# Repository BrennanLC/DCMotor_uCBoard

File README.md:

DCMotor_uCBoard
===============

ATmega328P Microcontroller Board with 2-CH DC Motor Driver

Design has not yet been verified. Build at your own risk!

Files:

MDM00001.sch - Board schematic eagle file

MDM00001.pdf - Board schematic PDF file

MDM00001.brd - Board layout eagle file

MDM00001Board.pdf - Board layout PDF file

schematic and board layout built with Eagle 6.4.0 Standard. More info and 
download available here:

https://www.cadsoftusa.com/

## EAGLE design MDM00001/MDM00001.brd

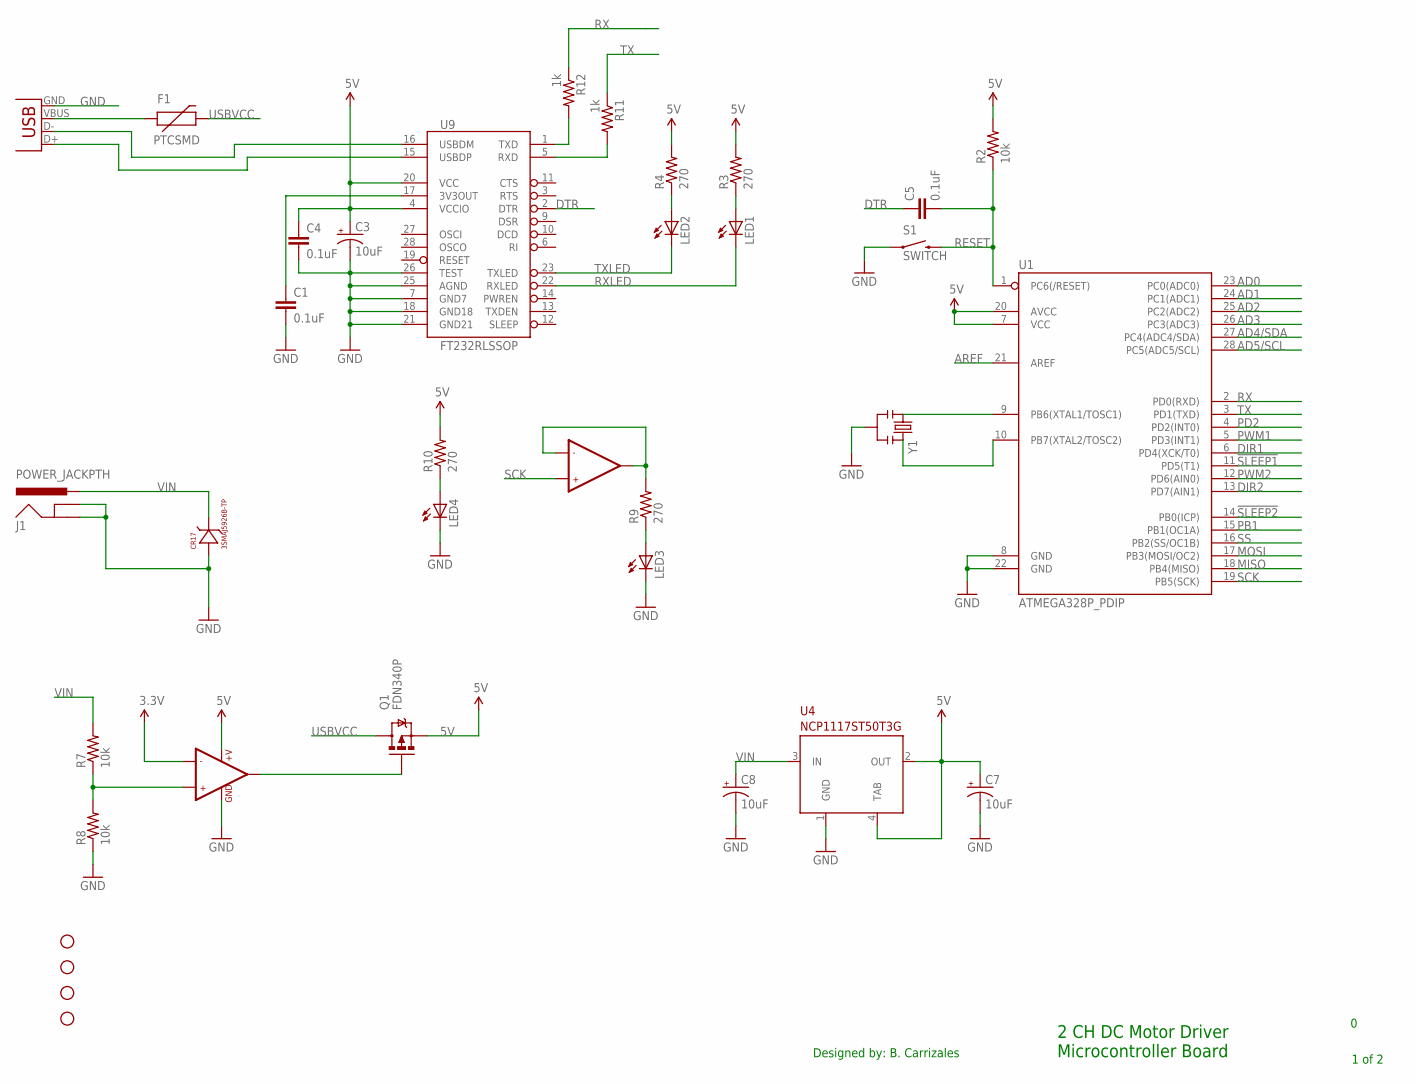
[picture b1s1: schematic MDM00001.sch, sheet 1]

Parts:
C1, C4, C5: 0.1uF; 0603-CAP
C3, C7, C8: 10uF; PANASONIC_BMIN
CR17: 3SMAJ5926B-TP; DO-214AC
F1: PTCSMD; PTC-1206
J1: POWER_JACKPTH; POWER_JACK_PTH
JP2: USBSMD; USB-MINIB
LED1, LED2, LED3, LED4: LED0603; LED-0603
Q1: FDN340P; SOT23-3
R2, R7, R8: 10k; 0603-RES
R3, R4, R9, R10: 270; 0603-RES
R11, R12: 1k; 0603-RES
S1: SWITCH; TACTILE-PTH
STANDOFF1, STANDOFF2, STANDOFF3, STANDOFF4: STAND-OFF
U1: ATMEGA328P_PDIP; DIL28-3
U4: NCP1117ST50T3G; SOT223
U9: FT232RLSSOP; SSOP28DB
U$3: LMV358; SO08
Y1: RESONATORPTH; RESONATOR-PTH

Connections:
3.3V: U$3.2 (-IN1)
5V: C3.+, C4.1, C7.+, Q1.2 (S), R2.2, R3.2, R4.2, R10.2, U1.7 (VCC), U1.20 (AVCC), U4.2 (OUT), U4.4 (TAB), U9.4 (VCCIO), U9.20 (VCC), U$3.8 (+V); also elsewhere on the board
!SLEEP1: U1.11 (PD5(T1)); also elsewhere on the board
!SLEEP2: U1.14 (PB0(ICP)); also elsewhere on the board
AD0: U1.23 (PC0(ADC0)); also elsewhere on the board
AD1: U1.24 (PC1(ADC1)); also elsewhere on the board
AD2: U1.25 (PC2(ADC2)); also elsewhere on the board
AD3: U1.26 (PC3(ADC3))
AD4/SDA: U1.27 (PC4(ADC4/SDA))
AD5/SCL: U1.28 (PC5(ADC5/SCL))
AREF: U1.21 (AREF)
DIR1: U1.6 (PD4(XCK/T0)); also elsewhere on the board
DIR2: U1.13 (PD7(AIN1)); also elsewhere on the board
DTR: C5.1, U9.2 (DTR)
GND: C1.2, C3.-, C4.2, C7.-, C8.-, CR17.AN, J1.GND, J1.GNDBREAK, JP2.GND, LED3.C, LED4.C, R8.1, S1.1, U1.8 (GND), U1.22 (GND), U4.1 (GND), U9.7 (GND7), U9.18 (GND18), U9.21 (GND21), U9.25 (AGND), U9.26 (TEST), U$3.4 (GND), Y1.2; also elsewhere on the board
MISO: U1.18 (PB4(MISO)); also elsewhere on the board
MOSI: U1.17 (PB3(MOSI/OC2)); also elsewhere on the board
unnamed: U1.9 (PB6(XTAL1/TOSC1)), Y1.1
unnamed: U1.10 (PB7(XTAL2/TOSC2)), Y1.3
unnamed: JP2.D-, U9.16 (USBDM)
unnamed: JP2.D+, U9.15 (USBDP)
unnamed: F1.1, JP2.VBUS
unnamed: LED2.A, R4.1
unnamed: LED1.A, R3.1
unnamed: R12.2, U9.1 (TXD)
unnamed: R11.2, U9.5 (RXD)
unnamed: R7.1, R8.2, U$3.3 (+IN1)
unnamed: LED3.A, R9.1
unnamed: R9.2, U$3.6 (-IN2), U$3.7 (OUT2)
unnamed: Q1.1 (G), U$3.1 (OUT1)
unnamed: LED4.A, R10.1
unnamed: C1.1, U9.17 (3V3OUT)
PB1: U1.15 (PB1(OC1A))
PD2: U1.4 (PD2(INT0))
PWM1: U1.5 (PD3(INT1)); also elsewhere on the board
PWM2: U1.12 (PD6(AIN0)); also elsewhere on the board
RESET: C5.2, R2.1, S1.3 (2), U1.1 (PC6(/RESET)); also elsewhere on the board
RX: R12.1, U1.2 (PD0(RXD))
RXLED: LED1.C, U9.22 (RXLED)
SCK: U1.19 (PB5(SCK)), U$3.5 (+IN2); also elsewhere on the board
SS: U1.16 (PB2(SS/OC1B))
TX: R11.1, U1.3 (PD1(TXD))
TXLED: LED2.C, U9.23 (TXLED)
USBVCC: F1.2, Q1.3 (D)
VIN: C8.+, CR17.CAT, J1.PWR, R7.2, U4.3 (IN); also elsewhere on the board

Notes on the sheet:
2 CH DC Motor Driver Microcontroller Board
1 of 2
Designed by: B. Carrizales

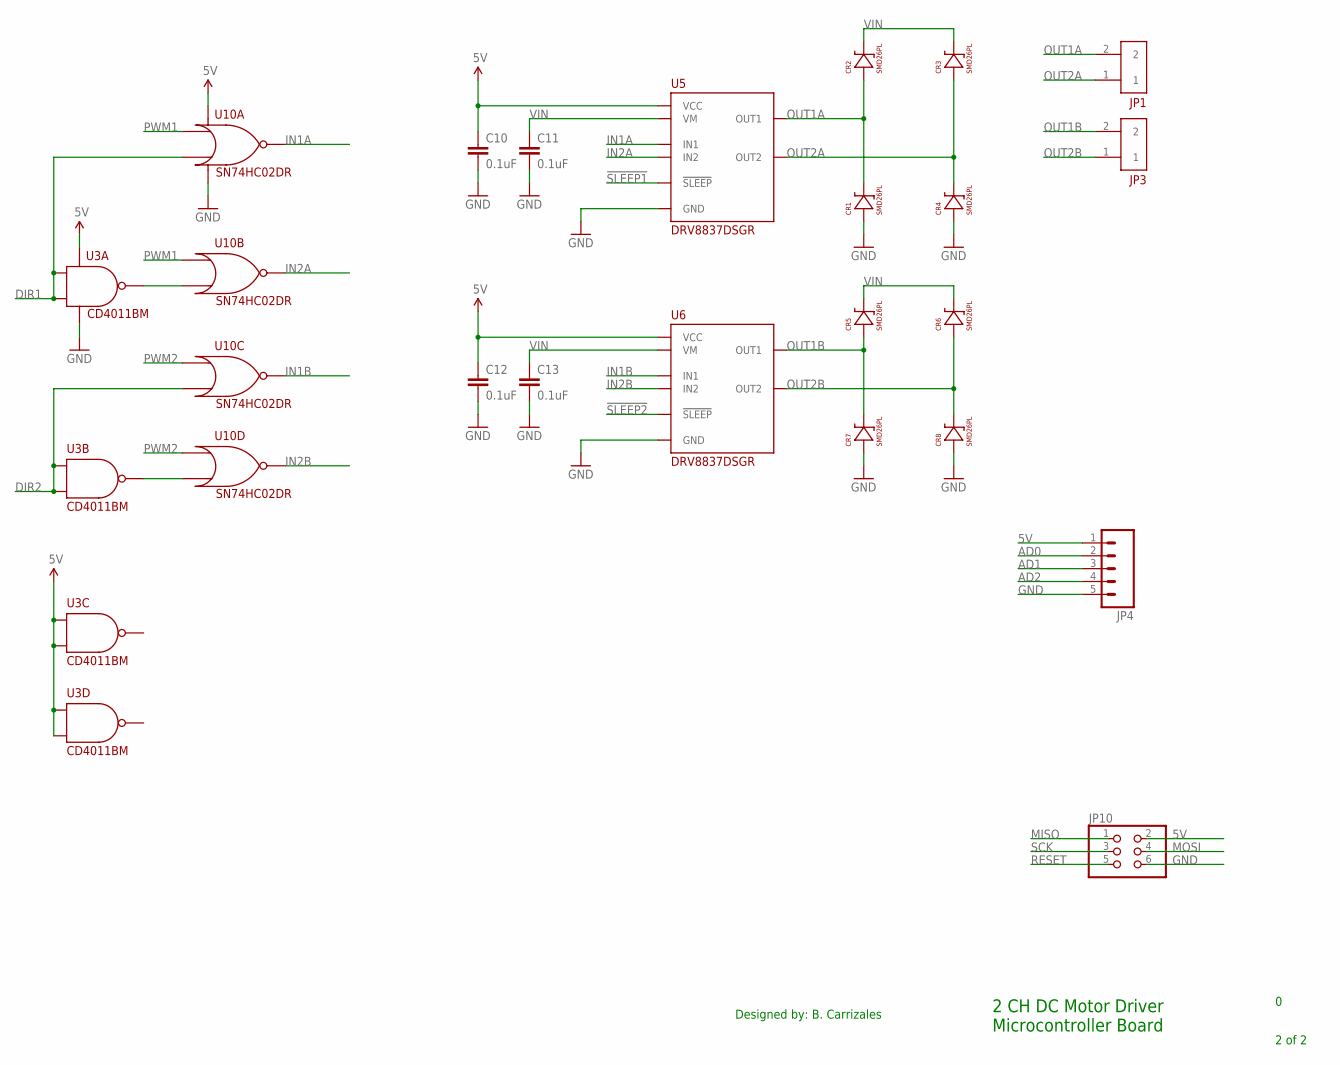
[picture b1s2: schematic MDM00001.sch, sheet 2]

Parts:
C10, C11, C12, C13: 0.1uF; 0603-CAP
CR1, CR2, CR3, CR4, CR5, CR6, CR7, CR8: SMD26PL; SOD-123FL
JP1, JP3: 2-TERMINAL; OSTTA020161
JP4: M05PTH; 1X05
JP10: PINHD-2X3; 2X03
U3: CD4011BM; 14-SOIC
U5, U6: DRV8837DSGR; 8-WSON
U10: SN74HC02DR; 14-SOIC

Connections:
5V: C10.1, C12.1, JP4.1, JP10.2, U3.8 (I0), U3.9 (I1), U3.12 (I0), U3.13 (I1), U3.14, U5.P$8 (VCC), U6.P$8 (VCC), U10.14; also elsewhere on the board
!SLEEP1: U5.P$7 (!SLEEP); also elsewhere on the board
!SLEEP2: U6.P$7 (!SLEEP); also elsewhere on the board
AD0: JP4.2; also elsewhere on the board
AD1: JP4.3; also elsewhere on the board
AD2: JP4.4; also elsewhere on the board
DIR1: U3.1 (I0), U3.2 (I1), U10.3 (I1); also elsewhere on the board
DIR2: U3.5 (I0), U3.6 (I1), U10.9 (I1); also elsewhere on the board
GND: C10.2, C11.2, C12.2, C13.2, CR1.1, CR4.1, CR7.1, CR8.1, JP4.5, JP10.6, U3.7, U5.P$4 (GND), U6.P$4 (GND), U10.7; also elsewhere on the board
IN1A: U5.P$6 (IN1), U10.1 (O1)
IN1B: U6.P$6 (IN1), U10.10 (O1)
IN2A: U5.P$5 (IN2), U10.4 (O1)
IN2B: U6.P$5 (IN2), U10.13 (O1)
MISO: JP10.1; also elsewhere on the board
MOSI: JP10.4; also elsewhere on the board
unnamed: U3.4 (O1), U10.12 (I1)
unnamed: U3.3 (O1), U10.6 (I1)
OUT1A: CR1.2, CR2.1, JP1.2, U5.P$2 (OUT1)
OUT1B: CR5.1, CR7.2, JP3.2, U6.P$2 (OUT1)
OUT2A: CR3.1, CR4.2, JP1.1, U5.P$3 (OUT2)
OUT2B: CR6.1, CR8.2, JP3.1, U6.P$3 (OUT2)
PWM1: U10.2 (I0), U10.5 (I0); also elsewhere on the board
PWM2: U10.8 (I0), U10.11 (I0); also elsewhere on the board
RESET: JP10.5; also elsewhere on the board
SCK: JP10.3; also elsewhere on the board
VIN: C11.1, C13.1, CR2.2, CR3.2, CR5.2, CR6.2, U5.P$1 (VM), U6.P$1 (VM); also elsewhere on the board

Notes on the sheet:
2 CH DC Motor Driver Microcontroller Board
2 of 2
Designed by: B. Carrizales

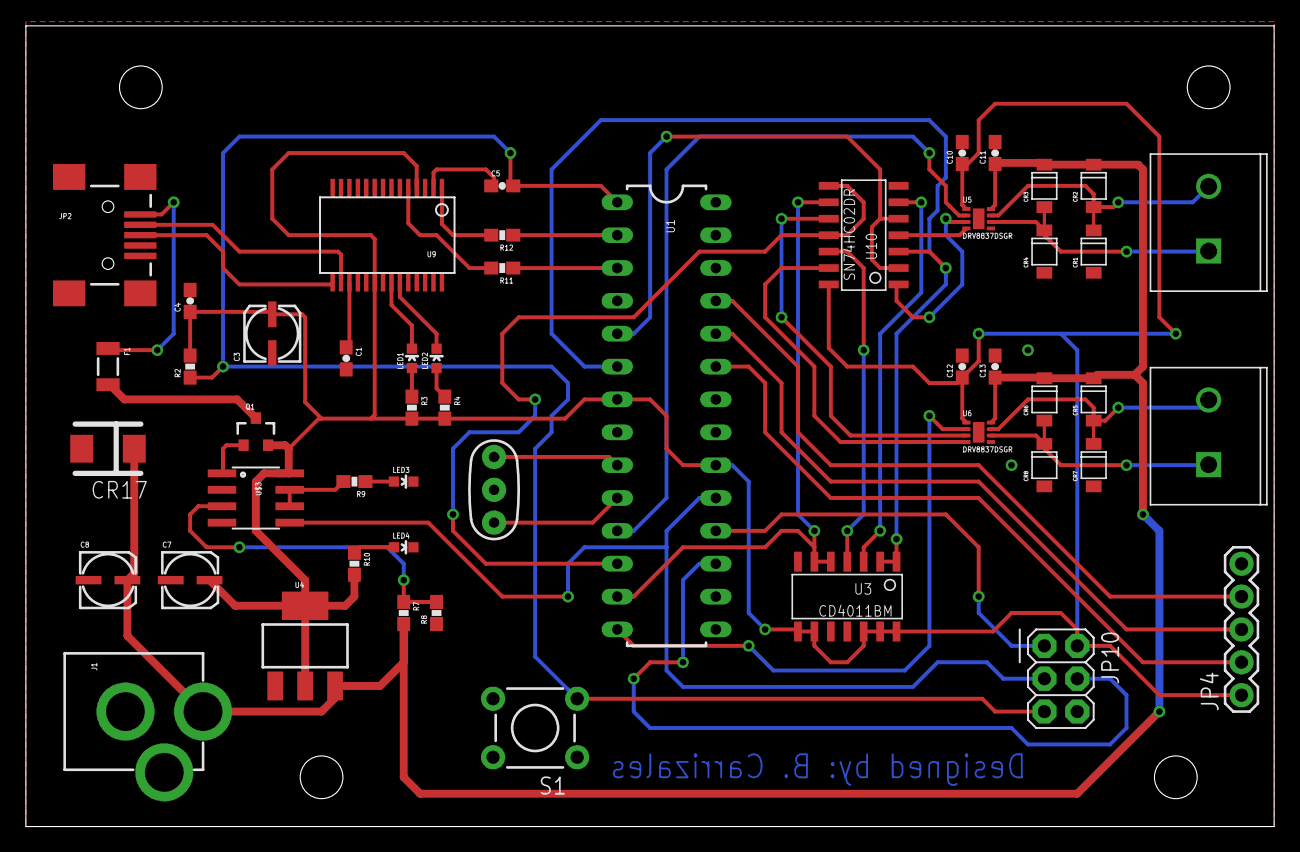
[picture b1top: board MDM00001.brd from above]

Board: 2 copper layers, 96.5 x 61.9 mm, 54 parts (0 on the bottom side), 47 nets.

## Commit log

2014-01-10 Initial Commit
    Initial Commit
2014-01-12 Finished Schematic
    Revision 0 of schematic complete. Generated bill of materials
2014-01-14 Finished Major Layout
    Finished major layout and updated schematic. Regenerated BOM.
2014-02-20 Updated README and added PDF Files
2014-02-27 Updated PDF Files

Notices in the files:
parts and their libraries:
SparkFun-DigitalIC: Licensing: CC v3.0 Share-Alike You are welcome to use this library for commercial purposes.
